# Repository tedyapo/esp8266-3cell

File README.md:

# esp8266-3cell
Carrier board for ESP-12x modules with 3 AA(A) cell low-quiescent current switching power supply

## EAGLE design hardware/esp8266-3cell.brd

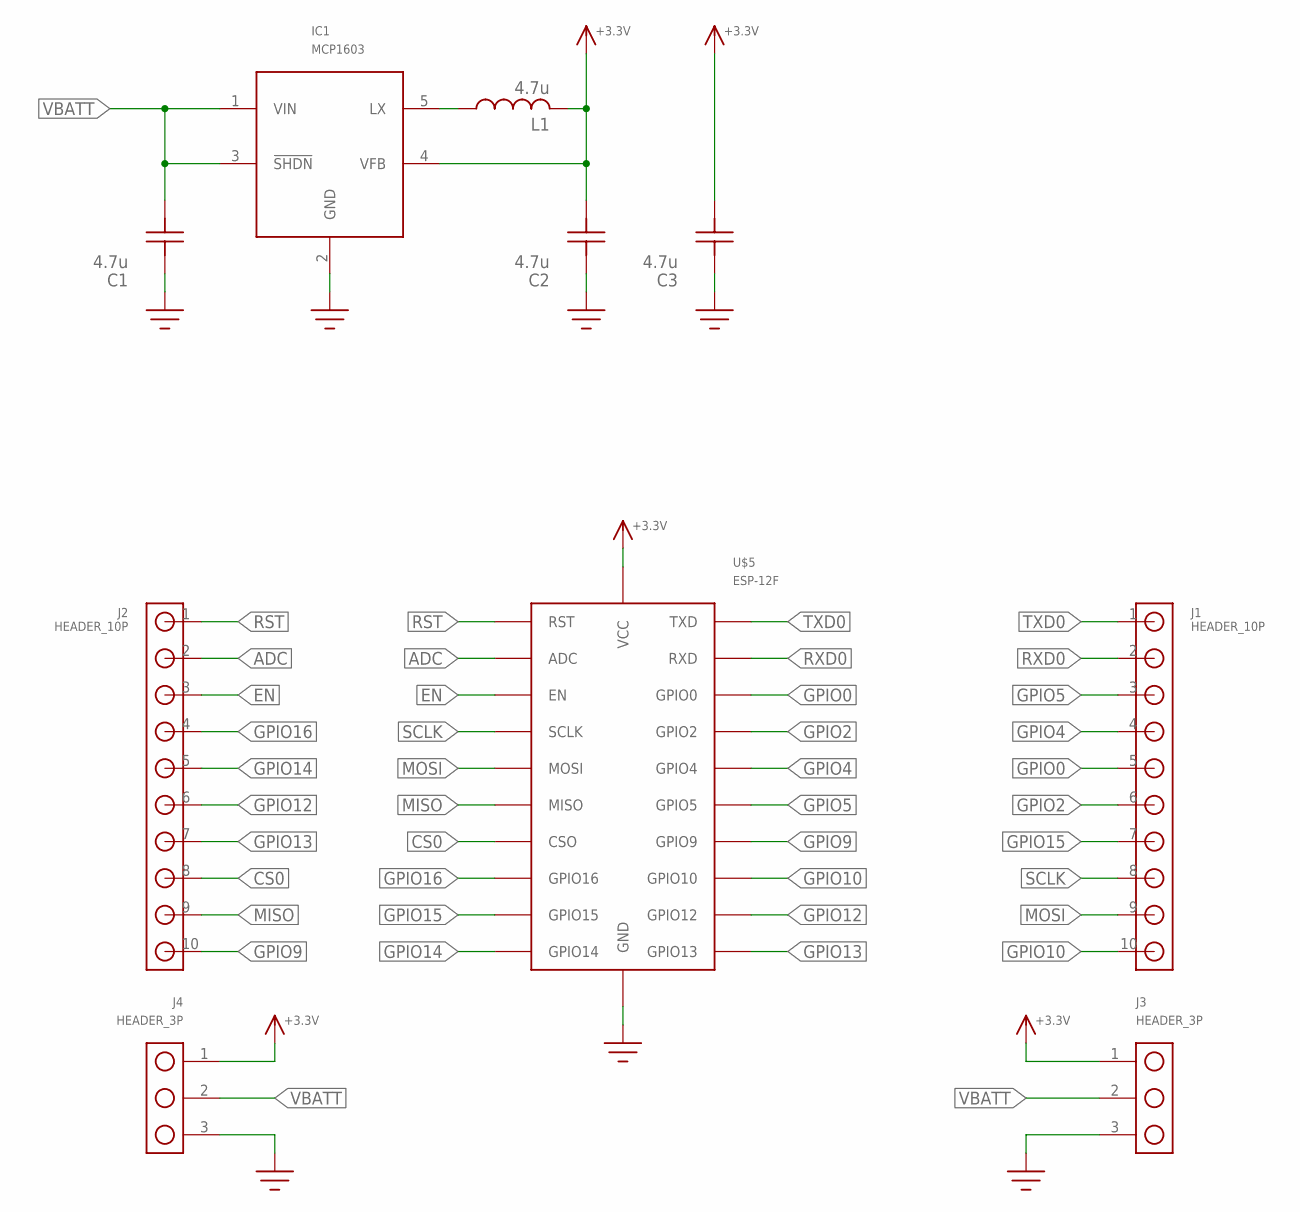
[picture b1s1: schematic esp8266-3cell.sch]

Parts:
C1, C2, C3: 4.7u; 0805
IC1: MCP1603; SOT23-5
J1, J2: HEADER_10P
J3, J4: HEADER_3P
L1: 4.7u; L24X24
U$5: ESP-12F

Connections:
+3.3V: C2.P$1, C3.P$1, IC1.4 (VFB), J3.1, J4.1, L1.2, U$5.VCC
ADC: J2.2, U$5.ADC
CS0: J2.8, U$5.CSO
EN: J2.3, U$5.EN
GND: C1.P$2, C2.P$2, C3.P$2, IC1.2 (GND), J3.3, J4.3, U$5.GND
GPIO0: J1.5, U$5.GPIO0
GPIO2: J1.6, U$5.GPIO2
GPIO4: J1.4, U$5.GPIO4
GPIO5: J1.3, U$5.GPIO5
GPIO9: J2.10, U$5.GPIO9
GPIO10: J1.10, U$5.GPIO10
GPIO12: J2.6, U$5.GPIO12
GPIO13: J2.7, U$5.GPIO13
GPIO14: J2.5, U$5.GPIO14
GPIO15: J1.7, U$5.GPIO15
GPIO16: J2.4, U$5.GPIO16
MISO: J2.9, U$5.MISO
MOSI: J1.9, U$5.MOSI
unnamed: IC1.5 (LX), L1.1
RST: J2.1, U$5.RST
RXD0: J1.2, U$5.RXD
SCLK: J1.8, U$5.SCLK
TXD0: J1.1, U$5.TXD
VBATT: C1.P$1, IC1.1 (VIN), IC1.3 (!SHDN!), J3.2, J4.2

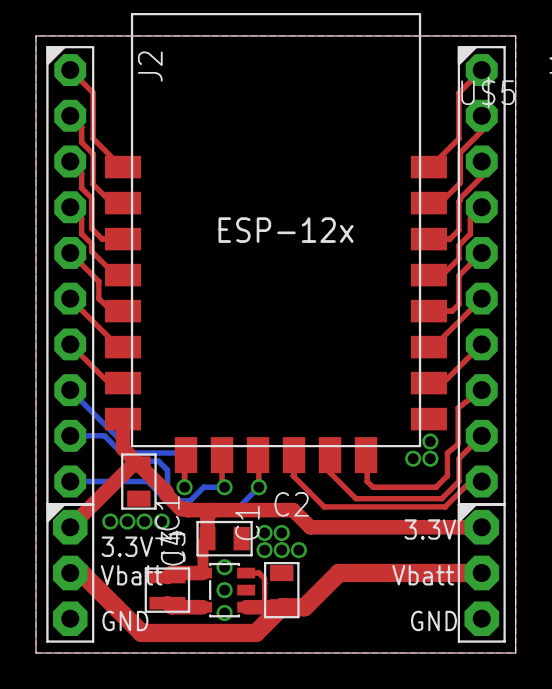
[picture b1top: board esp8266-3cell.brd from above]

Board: 2 copper layers, 26.6 x 34.3 mm, 10 parts (0 on the bottom side), 24 nets.

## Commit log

2018-03-10 checkpoint
2018-03-10 improved layout near input capacitor
